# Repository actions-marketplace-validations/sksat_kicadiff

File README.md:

# kicadiff

Visual diff tool for KiCad projects — see what changed between two
states of a `.kicad_pcb` / `.kicad_sch` / `.kicad_sym` / `.kicad_mod`
file in your browser, or as a markdown report you can paste into a PR.

[日本語版 README](./README.ja.md)

## What you get

- **HTML viewer** with side-by-side / overlay / swipe modes, layer toggles
  for PCBs, page navigation for hierarchical schematics, wheel-to-zoom and
  right-click-drag-to-pan, and an amber tab marker on files / pages whose
  rendered output actually changed.
- **Markdown report** (`--md`) with side-by-side image tables and a
  structural component diff (added / removed / changed by reference
  designator). Good for PR descriptions and commit messages.
- **Text-only structural diff** (`--text-only`) — fast, no image
  rendering, prints to stdout.

## Requirements

- [`kicad-cli`](https://www.kicad.org/) 9.x or later (rendering engine).
- [Bun](https://bun.sh) — runs the TypeScript CLI directly via shebang.
  Bun also compiles the standalone binary, so no separate Node install
  is needed for any workflow. Standalone binary users skip this.

The render pipeline (SVG → PNG, tri-colour pixel diff highlight) used to
need `rsvg-convert` and ImageMagick; both are now in-process
(`@resvg/resvg-js` for rasterisation, a small custom classifier on top
of `pngjs` for the diff overlay).

## Install

Three ways depending on what's already on your machine:

```sh
# 1. One-shot via Bun's package runner (no install)
bunx kicadiff [args...]

# 2. Global install (puts `kicadiff` on PATH)
pnpm add -g kicadiff
# or with `bun add -g kicadiff` / `npm install -g kicadiff`

# 3. Standalone binary — single file, no Bun runtime needed.
#    Drops `kicadiff` into ~/.local/bin (override with KICADIFF_INSTALL_DIR).
curl -fsSL https://raw.githubusercontent.com/sksat/kicadiff/main/install.sh | sh
```

`kicad-cli` (and `rsvg-convert` / `magick`) are not bundled — install KiCad 9+
first, then pick whichever kicadiff distribution form fits your workflow.

## Usage

`kicadiff` works on the same positional argument shape as `git diff`,
plus a few subcommands when you want to scope to one file type.

```sh
# Project-level diff (cwd, both PCB and schematic, default = HEAD vs working tree)
kicadiff

# Pass a project root, a .kicad_pro, or any single KiCad file
kicadiff path/to/project/
kicadiff project.kicad_pro
kicadiff project.kicad_pcb

# Compare arbitrary refs
kicadiff main path/to/project/         # working tree vs main
kicadiff v1.0 v2.0 board.kicad_pcb     # v1.0 vs v2.0
kicadiff main..feat foo.kicad_pcb      # range syntax
kicadiff main -- foo.kicad_pcb         # explicit `--` separator

# Subcommands scope to one file type (skip sibling auto-detect)
kicadiff pcb foo.kicad_pcb
kicadiff sch foo.kicad_sch       # alias: schematic
kicadiff sym lib.kicad_sym       # alias: symbol
kicadiff fp foo.kicad_mod        # alias: footprint
kicadiff fp lib.pretty           # whole .pretty/ library

# Output formats
kicadiff project/                       # default: HTML viewer + images
kicadiff project/ --md                  # markdown report + images, no HTML
kicadiff project/ --md --output report.md
kicadiff project/ --md --output -       # markdown to stdout, logs to stderr
kicadiff project/ --text                # also print structural text diff
kicadiff project/ --text-only           # text only, skip rendering (fast)
kicadiff project/ --images-only         # PNGs only, no HTML / markdown

# Custom markdown templates (Mustache subset: {{var}}, {{#section}}…{{/section}},
# {{^inverted}}…{{/inverted}}). Project template sees from_label / to_label /
# file_count / has_changes / files / file_sections. File template sees path /
# type / before_image / after_image / has_both / after_only / before_only /
# added_count / removed_count / changed_count / unchanged_count /
# has_structural_diff (real component changes) / has_visual_diff (PNGs differ) /
# has_changes (any of the above) / structural_diff (formatted body). Either
# flag is optional; the default template ships built-in.
kicadiff project/ --md --md-template my-report.md.tpl
kicadiff project/ --md --md-file-template my-file.md.tpl

# Auto-open the HTML in VSCode (Live Preview), a browser, etc.
kicadiff project/ --open vscode
kicadiff project/ --open firefox
kicadiff project/ --open=/usr/bin/open  # arbitrary command

# Watch mode — re-render every time an input file changes. Hot reload comes
# from the viewer: VSCode Live Preview / live-server / similar will refresh
# the page automatically once kicadiff overwrites the images. For plain
# file:// browsers, kicadiff injects a tiny image-polling script so the
# rendered images update in place without needing F5.
kicadiff project/ --watch
kicadiff project/ --watch --open vscode

# Other
kicadiff project/ -v                    # verbose summary (full PNG paths)
kicadiff project/ -q                    # suppress summary
kicadiff project/ --no-cache            # bypass the render cache

# Claude Code PostToolUse hook integration. Reads the hook JSON from
# stdin, renders only when the edited file is .kicad_pcb / .kicad_sch.
# Default: --open vscode (override with --open <target> as usual).
kicadiff hook
```

## Output

By default kicadiff writes to `<repo>/.claude/preview/` (next to the git
root) so the directory is easy to find from the project. Override with
`--output-dir <dir>` for the image directory, and `--output <path>` to
relocate the HTML / markdown file specifically (image paths in the
file get rewritten to be relative to it, so the file stays portable).

The HTML viewer is a single file with the manifest + image references
inline; you can email it, host it as a static asset, or open it
locally with VSCode's Live Preview extension.

## Render cache

Every per-side render is content-addressed and cached under
`$XDG_CACHE_HOME/kicadiff` (or `~/.cache/kicadiff`). Repeat runs
against unchanged content return in ~1 s vs ~5 s cold. Bypass with
`--no-cache` or override the location with `KICADIFF_CACHE_DIR`.

## GitHub Actions

Drop the action into a workflow to render a visual diff for every PR
that touches a KiCad file. The action handles KiCad install, runs
kicadiff, and (opt-in) uploads the rendered images as a build artifact,
writes a job summary with inline before/after images, upserts a sticky
PR comment, and updates a marked section in the PR description.

```yaml
# .github/workflows/kicad-diff.yml
name: KiCad visual diff
on:
  pull_request:
    paths: ["**/*.kicad_pcb", "**/*.kicad_sch"]
permissions:
  contents: read
  pull-requests: write   # only needed for pr-comment / pr-description
jobs:
  diff:
    runs-on: ubuntu-latest
    steps:
      - uses: actions/checkout@v6
        with: { fetch-depth: 0 }
      - uses: sksat/kicadiff@v0.1.0
        with:
          path: hardware/main-board   # default: cwd
          upload-artifact: 'true'
          pr-comment:      'true'
          pr-description:  'true'
```

Job summary embeds combined PNGs as base64 data URIs (no extra hosting
needed) up to a 1 MiB cap; if a project's images would overflow, the
action drops the rest, emits `::warning::`, and links to the artifact
for the full set. PR comment / description are kept text-only and link
to the artifact for images.

`install-kicadiff: bunx` (default) pulls the latest published kicadiff
on demand; pin a version with `install-kicadiff: <semver>`. Pre-installed
on PATH? Use `install-kicadiff: skip`.

## More

- `DESIGN.md` — architecture, render pipeline, cache key shape,
  manifest schema, viewer mode semantics
- `examples/blink/` — minimal KiCad project used as the test fixture
  and a usable starting point. Ships with a `.claude/settings.json`
  PostToolUse hook (`kicadiff hook`) that re-renders the diff every
  time a `.kicad_pcb` / `.kicad_sch` is Edited / Written.
- `examples/mcu-board/` — a more realistic small-board layout: an
  8-pin MCU stand-in with the usual stuff around it (5 V → 3.3 V
  AMS1117 LDO, decoupling caps, reset switch with pull-up, status
  LED, and a 6-pin programming/breakout header). Hierarchical
  schematic — root for the power chain and MCU itself,
  `peripherals.kicad_sch` sub-sheet for the reset/LED/header — so
  the per-page tabs in the viewer have something to switch between.

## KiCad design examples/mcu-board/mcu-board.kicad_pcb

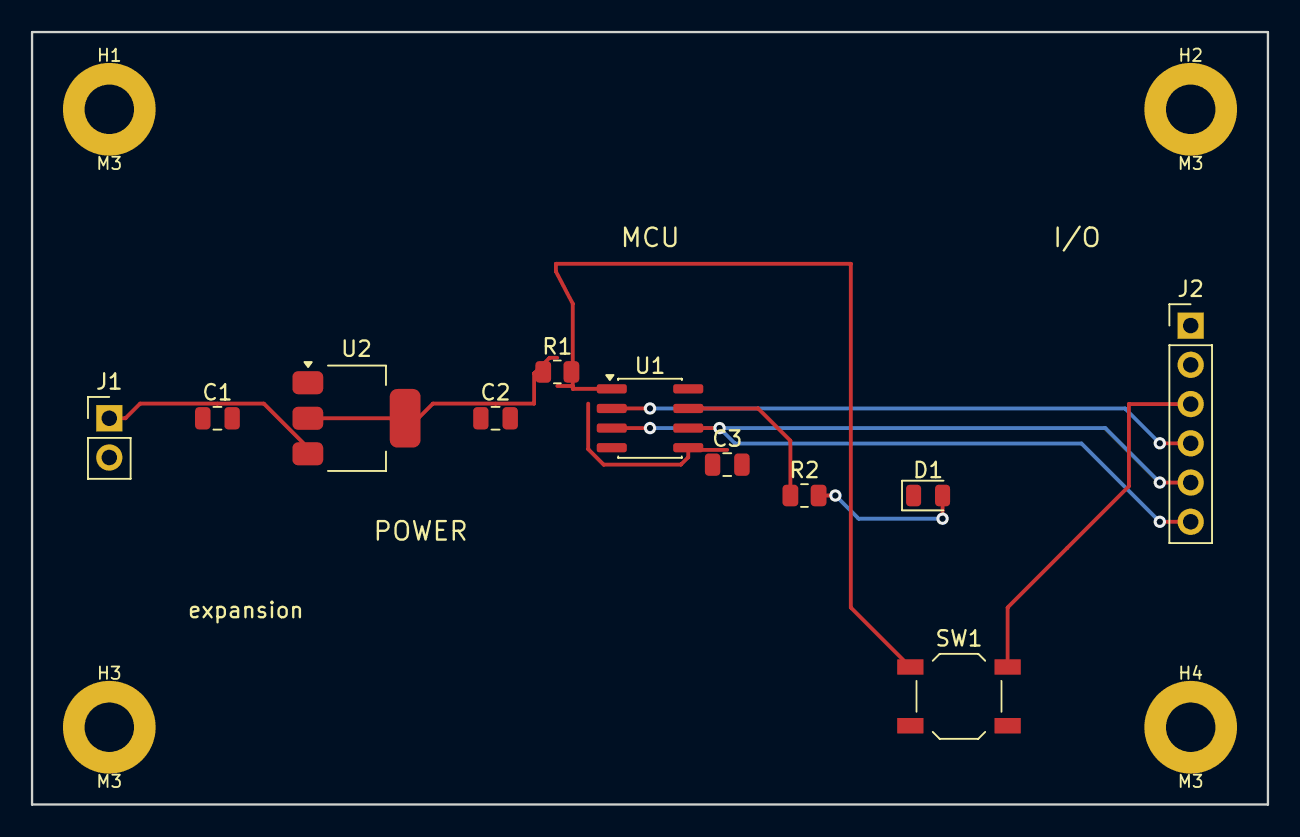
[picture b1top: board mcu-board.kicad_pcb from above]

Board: 2 copper layers, 80.0 x 50.0 mm, 15 parts (0 on the bottom side), 8 nets.

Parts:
C1, C2: 10uF; C_0805_2012Metric
C3: 100nF; C_0805_2012Metric
D1: Green; LED_0805_2012Metric
H1, H2, H3, H4: M3; MountingHole_3.2mm_M3
J1: 5V_IN; PinHeader_1x02_P2.54mm_Vertical
J2: PROG/IO; PinHeader_1x06_P2.54mm_Vertical
R1: 10k; R_0805_2012Metric
R2: 1k; R_0805_2012Metric
SW1: Reset; SW_SPST_TL3342
U1: MCU; SOIC-8_3.9x4.9mm_P1.27mm
U2: AMS1117-3.3; SOT-223-3_TabPin2

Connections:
+3V3: C2.1, C3.1, J2.1, R1.1, U1.5, U2.2
+5V: C1.1, J1.1, U2.3
/LED_A: R2.1, U1.7
/PA1: J2.4, U1.2
/PA2: J2.5, U1.3
/PA3: J2.6, U1.6
/RST: J2.3, R1.2, SW1.1, U1.1
GND: C1.2, C2.2, C3.2, D1.1, D1.2, J1.2, J2.2, R2.2, SW1.2, U1.4, U2.1

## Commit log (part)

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2026-05-10 Add renovate.json
2026-05-10 Revert "feat(action): image-host=branch pushes preview to orphan sibling branch"
    This reverts commit 6f7da0914f6f1a0048d63e5c9c8eb9d73b202977.
2026-05-10 chore(kicadiff): update preview images
2026-05-10 chore(deps): pin dependencies
2026-05-17 Inject CodeQL file
